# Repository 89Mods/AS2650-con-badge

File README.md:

## AS2650 Con Badge

Repo containing all the files for my latest con badge, using one of my GFMPW-0 ICs.

`HW` contains the KiCad project for the hardware.

`NB_Firmware` contains the management controller firmware.

`CPLD` contains the Quartus project for the CPLD on the board.

`Verilog` contains a complete Verilog model of the whole board, including the LED screen (requires gtkmm-4.0 to display).

`Software` is the actual meat of the project - all the code running on the badge.

`Bitmaps` contains all image assets to be placed into ROM.

Some misc stuff:

`ObjParser.java` converts .obj 3D model files to the format used by my rasterizer implementation.

`ROM_layout` visualizes the layout of the SPI flash accessible by the AS2650.

`ROMGlue` is a very long script that grabs all the different built binaries and asset files, and puts it also into a single ROM image, according to the documented layout.

`Avali.bin` is the 3D model data rendered by one of the demos.

There is also a (very ugly) Makefile to build parts of the project.

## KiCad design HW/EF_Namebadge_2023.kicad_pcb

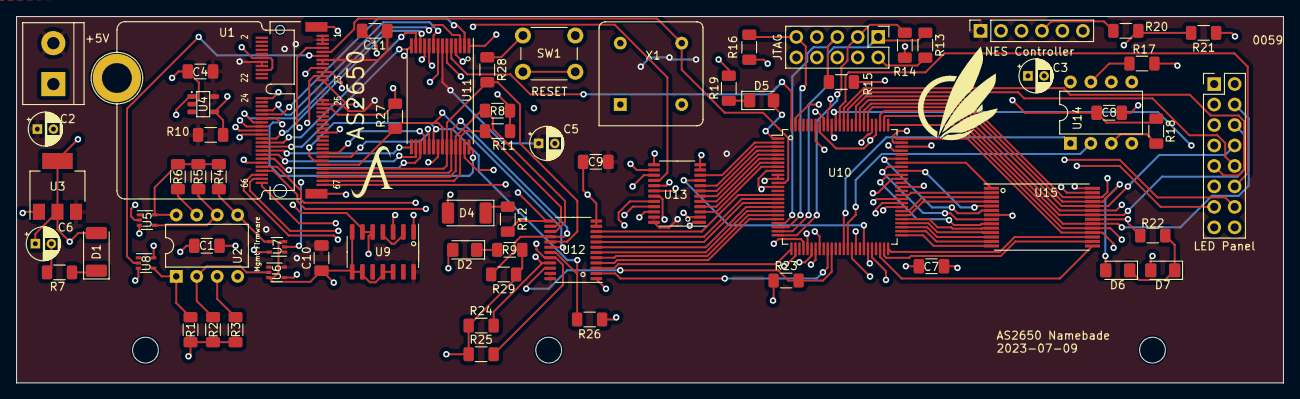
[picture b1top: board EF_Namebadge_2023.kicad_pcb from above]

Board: 4 copper layers, 157.2 x 45.5 mm, 71 parts (0 on the bottom side), 124 nets.

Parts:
C1, C4, C7, C8, C9, C10, C11: 0.1µF; C_1206_3216Metric_Pad1.33x1.80mm_HandSolder
C2, C5, C6: 1µF; CP_Radial_D4.0mm_P2.00mm
C3: 10µF; CP_Radial_D4.0mm_P2.00mm
D1, D4: LED; LED_2010_5025Metric_Pad1.52x2.65mm_HandSolder
D2, D5, D6, D7: LED; LED_1206_3216Metric_Pad1.42x1.75mm_HandSolder
H1: MICROMOD-Standoff; MicroMod-Standoff
H2, H3, H4: MountingHole; MountingHole_3.2mm_M3_ISO7380
J1: Screw_Terminal_01x02; TerminalBlock_bornier-2_P5.08mm
J2: JTAG; PinHeader_2x05_P2.54mm_Vertical
J3: LED Panel; PinHeader_2x08_P2.54mm_Vertical
J4: NES Controller; PinSocket_1x06_P2.54mm_Vertical
R1, R2, R4, R5: 100K; R_1206_3216Metric_Pad1.30x1.75mm_HandSolder
R3, R6, R7, R8, R9, R10, R11, R12, R13, R14, R15, R16, R17, R18, R23, R24, R25, R26, R27, R28, R29: 10K; R_1206_3216Metric_Pad1.30x1.75mm_HandSolder
R19, R20, R21, R22: 1K; R_1206_3216Metric_Pad1.30x1.75mm_HandSolder
SW1: SW_Push; SW_PUSH_6mm
U1: AS2650; M.2-CONNECTOR-E
U2, U14: W25Q32FVSS; DIP-8_W7.62mm
U3: AMS1117-3.3; SOT-223-3_TabPin2
U4: MCP1319MT-29LE-OT; PoR_5_SOT23
U5, U6, U7, U8: SN74LV1T34DCK; SOT-353_SC-70-5
U9: 74HC02; SOIC-14_3.9x8.7mm_P1.27mm
U10: EPM240T100; LQFP-100_14x14mm_P0.5mm
U11: AS7C256; TSOP-I-28_11.8x8mm_P0.55mm
U12, U13: SN74LVC8T245; TSSOP-24_4.4x7.8mm_P0.65mm
U15: 61LV256; TSOP-I-28_11.8x8mm_P0.55mm
X1: 25MHz; Oscillator_DIP-8

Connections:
+3V3: C1.1, C3.1, C6.1, C7.2, C8.2, D1.2 (A), J2.4, R1.2, R2.2, R3.2, R4.2, R5.2, R6.2, R14.2, R15.2, R16.2, R17.1, R18.2, R23.1, U2.8 (VCC), U3.2 (VO), U5.5 (VCC), U7.5 (VCC), U8.5 (VCC), U10.9 (VCCIO1), U10.13 (VCCINT), U10.31 (VCCIO1), U10.45 (VCCIO1), U10.59 (VCCIO2), U10.63 (VCCINT), U10.80 (VCCIO2), U10.94 (VCCIO2), U12.1 (Vcca), U13.1 (Vcca), U14.8 (VCC), U15.7 (Vdd), X1.8 (Vcc)
+5V: C2.1, C4.2, C5.1, C9.2, C10.2, C11.2, J1.2, J4.1, R10.2, U1.1 (vccd2), U1.3 (vddio), U1.5 (vdda), U1.13 (vdda2), U1.14 (vccd), U1.15 (vcdd), U1.16 (vddio), U1.33 (vdda1), U1.35 (vccd1), U3.3 (VI), U4.5 (VDD), U6.5 (VCC), U9.14 (VCC), U11.7 (Vcc), U12.23 (Vccb), U12.24 (Vccb), U13.23 (Vccb), U13.24 (Vccb)
A0: U1.62 (mprj_io[20]), U11.17 (A0)
A1: U1.60 (mprj_io[21]), U11.16 (A1)
A2: U1.58 (mprj_io[22]), U11.15 (A2)
A3: U1.56 (mprj_io[23]), U11.14 (A3)
A4: U1.54 (mprj_io[24]), U11.13 (A4)
A5: U1.52 (mprj_io[25]), U11.12 (A5)
A6: U1.50 (mprj_io[26]), U11.11 (A6)
A7: U1.48 (mprj_io[27]), U11.10 (A7)
A8: U1.46 (mprj_io[28]), U11.4 (A8)
A9: U1.44 (mprj_io[29]), U11.3 (A9)
A10: U1.42 (mprj_io[30]), U11.28 (A10)
A11: U1.40 (mprj_io[31]), U11.2 (A11)
A12: U1.38 (mprj_io[32]), U11.9 (A12), U13.16 (B6)
A12_3.3: U10.3 (IO1_3), U13.8 (A6)
A13: U10.100 (IO2_100), U11.5 (A13)
A14: U10.99 (IO2_99), U11.8 (A14)
BUS_DIR: U10.35 (IO1_35), U12.2 (DIR)
DB0: R24.2, U1.59 (mprj_io[5]_ser_rx), U11.18 (I/O0), U12.21 (B1)
DB0_3.3: U10.26 (IO1_26), U12.3 (A1)
DB1: R25.2, U1.61 (mprj_io[6]_ser_tx), U11.19 (I/O1), U12.20 (B2)
DB1_3.3: U10.21 (IO1_21), U12.4 (A2)
DB2: R26.2, U1.63 (mprj_io[7]), U11.20 (I/O2), U12.19 (B3)
DB2_3.3: U10.20 (IO1_20), U12.5 (A3)
DB3: R27.2, U1.65 (mprj_io[8]), U11.22 (I/O3), U12.18 (B4)
DB3_3.3: U10.19 (IO1_19), U12.6 (A4)
DB4: R28.2, U1.67 (mprj_io[9]), U11.23 (I/O4), U12.17 (B5)
DB4_3.3: U10.18 (IO1_18), U12.7 (A5)
DB5: R29.2, U1.69 (mprj_io[10]), U11.24 (I/O5), U12.16 (B6)
DB5_3.3: U10.17 (IO1_17), U12.8 (A6)
DB6: R8.2, U1.71 (mprj_io[11]), U11.25 (I/O6), U12.15 (B7)
DB6_3.3: U10.16 (IO1_16), U12.9 (A7)
DB7: R11.2, U1.73 (mprj_io[12]), U11.26 (I/O7), U12.14 (B8)
DB7_3.3: U10.15 (IO1_15), U12.10 (A8)
DISP_A: J3.10, U10.86 (IO2_86)
DISP_B: J3.9, U10.87 (IO2_87)
DISP_C: J3.12, U10.88 (IO2_88)
DISP_CLK: J3.14, U10.73 (IO2_73)
DISP_D: J3.11, U10.89 (IO2_89)
DISP_OE: J3.16, U10.74 (IO2_74)
DISP_STB: J3.13, U10.72 (IO2_72)
D/~C: U1.74 (mprj_io[14]), U13.21 (B1)
D/~C_3.3: U10.8 (IO1_8), U13.3 (A1)
FIRM_CS: R1.1, U2.1 (~CS), U8.4 (Y)
FIRM_SCK: R5.1, U2.6 (SCK), U5.4 (Y)
FIRM_SI: R4.1, U2.5 (SI(D0)), U7.4 (Y)
FIRM_SO: R2.1, U2.2 (SO(D1)), U6.2 (A)
Flag: D2.2 (A), U1.64 (mprj_io[19])
GND: C1.2, C2.2, C3.2, C4.1, C5.2, C6.2, C7.1, C8.1, C9.1, C10.1, C11.1, J1.1, J2.2, J2.10, J3.3, J3.7, J3.15, J4.5, J4.6, R7.2, R8.1, R9.2, R11.1, R12.2, R13.2, R19.2, R21.1, R22.2, R24.1, R25.1, R26.1, R27.1, R28.1, R29.1, SW1.1, U1.12 (GND), U1.18 (GND), U1.37 (GND), U1.A1 (GND), U1.A2 (GND), U2.4 (GND), U3.1 (GND), U4.2 (VSS), U5.3 (GND), U6.3 (GND), U7.3 (GND), U8.3 (GND), U9.7 (GND), U9.8, U9.9, U9.11, U9.12, U10.10 (GNDIO), U10.11 (GNDINT), U10.32 (GNDIO), U10.46 (GNDIO), U10.60 (GNDIO), U10.65 (GNDINT), U10.79 (GNDIO), U10.93 (GNDIO), U11.21 (GND), U12.11 (GND), U12.12 (GND), U12.13 (GND), U13.2 (DIR), U13.11 (GND), U13.12 (GND), U13.13 (GND), U13.22 (~OE), U14.4 (GND), U15.21 (GND), U15.27 (~CE), X1.4 (GND)
LVL_SHIFT_EN: R23.2, U10.36 (IO1_36), U12.22 (~OE)
M/~IO: U1.72 (mprj_io[15]), U13.20 (B2)
M/~IO_3.3: U10.7 (IO1_7), U13.4 (A2)
NES_CLK: J4.2, U10.29 (IO1_29)
NES_DATA: R20.1, R21.2, U10.33 (IO1_33)
NES_LATCH: J4.3, U10.30 (IO1_30)
unnamed: D1.1 (K), R7.1
unnamed: D2.1 (K), R9.1
unnamed: D4.1 (K), R12.1
unnamed: D5.2 (A), U10.1 (IO2_1)
unnamed: D5.1 (K), R19.1
unnamed: D6.1 (K), D7.1 (K), R22.1
unnamed: J2.1, R13.1, U10.24 (TCK)
unnamed: J2.3, R14.1, U10.25 (TDO)
unnamed: J2.5, R15.1, U10.22 (TMS)
unnamed: J2.9, R16.1, U10.23 (TDI)
unnamed: J4.4, R20.2
unnamed: U1.11 (Caravel_CSB), U8.2 (A)
unnamed: U1.17 (Caravel_D0), U7.2 (A)
unnamed: U1.19 (Caravel_D1), U6.4 (Y)
unnamed: U1.23 (Caravel_SCK), U5.2 (A)
unnamed: U1.7 (~RST), U9.1
unnamed: R6.1, U2.7 (~HOLD(D3))
unnamed: R3.1, U2.3 (~WP(D2))
unnamed: R10.1, SW1.2, U4.4 (~MR)
unnamed: U9.2, U9.4
unnamed: U10.2 (IO1_2), U13.10 (A8)
unnamed: R17.2, U14.7 (~HOLD(D3))
unnamed: R18.1, U14.3 (~WP(D2))
OPREQ: U1.68 (mprj_io[17]), U13.18 (B4)
OPREQ_3.3: U10.5 (IO1_5), U13.6 (A4)
POR: U4.1 (~RST), U9.5, U9.6, U13.15 (B7)
POR_3.3: U10.44 (IO1_44/DEV_CLRn), U13.9 (A7)
R/~W: U1.66 (mprj_io[18]), U13.17 (B5)
R/~W_3.3: U10.4 (IO1_4), U13.7 (A5)
SPI_SCK: U10.41 (IO1_41), U14.6 (SCK)
SPI_SI: U10.40 (IO1_40), U14.2 (SO(D1))
SPI_SO: U10.42 (IO1_42), U14.5 (SI(D0))
Sense: U1.75 (mprj_io[13]), U10.27 (IO1_27)
VRAM_AD0: U10.50 (IO1_50), U15.17 (A0)
VRAM_AD1: U10.49 (IO1_49), U15.16 (A1)
VRAM_AD2: U10.48 (IO1_48), U15.15 (A2)
VRAM_AD3: U10.51 (IO1_51), U15.14 (A3)
VRAM_AD4: U10.52 (IO2_52), U15.13 (A4)
VRAM_AD5: U10.53 (IO2_53), U15.12 (A5)
VRAM_AD6: U10.54 (IO2_54), U15.11 (A6)
VRAM_AD7: U10.55 (IO2_55), U15.10 (A7)
VRAM_AD8: U10.56 (IO2_56), U15.4 (A8)
VRAM_AD9: U10.57 (IO2_57), U15.3 (A9)
VRAM_AD10: U10.58 (IO2_58), U15.28 (A10)
VRAM_AD11: U10.61 (IO2_61), U15.2 (A11)
VRAM_AD12: U10.66 (IO2_66), U15.9 (A12)
VRAM_AD13: U10.67 (IO2_67), U15.5 (A13)
VRAM_AD14: U10.68 (IO2_68), U15.8 (A14)
VRAM_D0: J3.2, U10.75 (IO2_75), U15.18 (IO0)
VRAM_D1: J3.1, U10.76 (IO2_76), U15.19 (IO1)
VRAM_D2: J3.4, U10.77 (IO2_77), U15.20 (IO2)
VRAM_D3: J3.6, U10.78 (IO2_78), U15.22 (IO3)
VRAM_D4: J3.5, U10.81 (IO2_81), U15.23 (IO4)
VRAM_D5: J3.8, U10.82 (IO2_82), U15.24 (IO5)
VRAM_D6: D6.2 (A), U10.83 (IO2_83), U15.25 (IO6)
VRAM_D7: D7.2 (A), U10.84 (IO2_84), U15.26 (IO7)
WRP: U1.70 (mprj_io[16]), U13.19 (B3)
WRP_3.3: U10.6 (IO1_6), U13.5 (A3)
cpld_rst: U1.32 (mprj_io[35]), U13.14 (B8)
crvl_led: D4.2 (A), U1.49 (mprj_io[0])
gpio: U1.21 (gpio), U9.3
xclk: U1.9 (xclk), U10.12 (IO1_12/GCLK0), X1.5 (OUT)
~RAM_CE: U10.90 (IO2_90), U11.27 (~CE)
~RAM_OE: U10.91 (IO2_91), U11.1 (~OE)
~RAM_WE: U10.92 (IO2_92), U11.6 (~WE)
~SPI_CS: U10.39 (IO1_39), U14.1 (~CS)
~VRAM_OE: U10.69 (IO2_69), U15.1 (~OE)
~VRAM_WE: U10.70 (IO2_70), U15.6 (~WE)

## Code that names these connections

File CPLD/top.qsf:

# -------------------------------------------------------------------------- #
#
# Copyright (C) 2023  Intel Corporation. All rights reserved.
# Your use of Intel Corporation's design tools, logic functions 
# and other software and tools, and any partner logic 
# functions, and any output files from any of the foregoing 
# (including device programming or simulation files), and any 
# associated documentation or information are expressly subject 
# to the terms and conditions of the Intel Program License 
# Subscription Agreement, the Intel Quartus Prime License Agreement,
# the Intel FPGA IP License Agreement, or other applicable license
# agreement, including, without limitation, that your use is for
# the sole purpose of programming logic devices manufactured by
# Intel and sold by Intel or its authorized distributors.  Please
# refer to the applicable agreement for further details, at
# https://fpgasoftware.intel.com/eula.
#
# -------------------------------------------------------------------------- #
#
# Quartus Prime
# Version 22.1std.1 Build 917 02/14/2023 SC Lite Edition
# Date created = 17:04:29  June 30, 2023
#
# -------------------------------------------------------------------------- #
#
# Notes:
#
# 1) The default values for assignments are stored in the file:
#		top_assignment_defaults.qdf
#    If this file doesn't exist, see file:
#		assignment_defaults.qdf
#
# 2) Intel recommends that you do not modify this file. This
#    file is updated automatically by the Quartus Prime software
#    and any changes you make may be lost or overwritten.
#
# -------------------------------------------------------------------------- #


set_global_assignment -name FAMILY "MAX II"
set_global_assignment -name DEVICE EPM240T100C5
set_global_assignment -name TOP_LEVEL_ENTITY top
set_global_assignment -name ORIGINAL_QUARTUS_VERSION 22.1STD.1
set_global_assignment -name PROJECT_CREATION_TIME_DATE "17:04:29  JUNE 30, 2023"
set_global_assignment -name LAST_QUARTUS_VERSION "22.1std.2 Lite Edition"
set_global_assignment -name PROJECT_OUTPUT_DIRECTORY output_files
set_global_assignment -name MIN_CORE_JUNCTION_TEMP 0
set_global_assignment -name MAX_CORE_JUNCTION_TEMP 85
set_global_assignment -name DEVICE_FILTER_PACKAGE TQFP
set_global_assignment -name DEVICE_FILTER_PIN_COUNT 100
set_global_assignment -name ERROR_CHECK_FREQUENCY_DIVISOR "-1"
set_global_assignment -name POWER_EXT_SUPPLY_VOLTAGE_TO_REGULATOR 3.3V
set_location_assignment PIN_5 -to opreq
set_location_assignment PIN_4 -to rw
set_location_assignment PIN_6 -to wrp
set_location_assignment PIN_12 -to clk
set_location_assignment PIN_15 -to dbus[7]
set_location_assignment PIN_16 -to dbus[6]
set_location_assignment PIN_17 -to dbus[5]
set_location_assignment PIN_18 -to dbus[4]
set_location_assignment PIN_19 -to dbus[3]
set_location_assignment PIN_20 -to dbus[2]
set_location_assignment PIN_21 -to dbus[1]
set_location_assignment PIN_26 -to dbus[0]
set_instance_assignment -name IO_STANDARD "3.3-V LVTTL" -to A12
set_instance_assignment -name IO_STANDARD "3.3-V LVTTL" -to DISP_addr[1]
set_location_assignment PIN_3 -to A12
set_location_assignment PIN_100 -to A13
set_location_assignment PIN_99 -to A14
set_location_assignment PIN_86 -to DISP_addr[0]
set_location_assignment PIN_87 -to DISP_addr[1]
set_location_assignment PIN_88 -to DISP_addr[2]
set_location_assignment PIN_89 -to DISP_addr[3]
set_location_assignment PIN_73 -to DISP_clk
set_location_assignment PIN_74 -to DISP_oeb
set_location_assignment PIN_72 -to DISP_stb
set_location_assignment PIN_29 -to NES_clk
set_location_assignment PIN_33 -to NES_data
set_location_assignment PIN_91 -to RAM_oeb
set_location_assignment PIN_90 -to RAM_ceb
set_location_assignment PIN_92 -to RAM_web
set_location_assignment PIN_27 -to sense
set_location_assignment PIN_7 -to m_io
set_location_assignment PIN_36 -to lvl_shift_enb
set_location_assignment PIN_2 -to cpld_rst
set_location_assignment PIN_8 -to d_c
set_location_assignment PIN_35 -to bus_dir
set_location_assignment PIN_70 -to VRAM_web
set_location_assignment PIN_69 -to VRAM_oeb
set_location_assignment PIN_84 -to VRAM_data[7]
set_location_assignment PIN_83 -to VRAM_data[6]
set_location_assignment PIN_82 -to VRAM_data[5]
set_location_assignment PIN_81 -to VRAM_data[4]
set_location_assignment PIN_78 -to VRAM_data[3]
set_location_assignment PIN_77 -to VRAM_data[2]
set_location_assignment PIN_76 -to VRAM_data[1]
set_location_assignment PIN_75 -to VRAM_data[0]
set_location_assignment PIN_68 -to VRAM_addr[14]
set_location_assignment PIN_67 -to VRAM_addr[13]
set_location_assignment PIN_66 -to VRAM_addr[12]
set_location_assignment PIN_44 -to POR
set_location_assignment PIN_30 -to NES_latch
set_location_assignment PIN_39 -to SPI_csb
set_location_assignment PIN_41 -to SPI_sck
set_location_assignment PIN_40 -to SPI_si
set_location_assignment PIN_42 -to SPI_so
set_location_assignment PIN_61 -to VRAM_addr[11]
set_location_assignment PIN_58 -to VRAM_addr[10]
set_location_assignment PIN_57 -to VRAM_addr[9]
set_location_assignment PIN_56 -to VRAM_addr[8]
set_location_assignment PIN_55 -to VRAM_addr[7]
set_location_assignment PIN_54 -to VRAM_addr[6]
set_location_assignment PIN_53 -to VRAM_addr[5]
set_location_assignment PIN_52 -to VRAM_addr[4]
set_location_assignment PIN_51 -to VRAM_addr[3]
set_location_assignment PIN_48 -to VRAM_addr[2]
set_location_assignment PIN_49 -to VRAM_addr[1]
set_location_assignment PIN_50 -to VRAM_addr[0]
set_location_assignment PIN_1 -to LED
set_instance_assignment -name IO_STANDARD "3.3-V LVTTL" -to RAM_ceb
set_instance_assignment -name IO_STANDARD "3.3-V LVTTL" -to RAM_oeb
set_instance_assignment -name IO_STANDARD "3.3-V LVCMOS" -to RAM_web
set_instance_assignment -name IO_STANDARD "3.3-V LVCMOS" -to A13
set_instance_assignment -name IO_STANDARD "3.3-V LVCMOS" -to A14
set_instance_assignment -name IO_STANDARD "3.3-V LVTTL" -to dbus[7]
set_instance_assignment -name IO_STANDARD "3.3-V LVTTL" -to dbus[6]
set_instance_assignment -name IO_STANDARD "3.3-V LVTTL" -to dbus[5]
set_instance_assignment -name IO_STANDARD "3.3-V LVTTL" -to dbus[4]
set_instance_assignment -name IO_STANDARD "3.3-V LVTTL" -to dbus[3]
set_instance_assignment -name IO_STANDARD "3.3-V LVTTL" -to dbus[2]
set_instance_assignment -name IO_STANDARD "3.3-V LVTTL" -to dbus[1]
set_instance_assignment -name IO_STANDARD "3.3-V LVTTL" -to dbus
set_global_assignment -name SDC_FILE top.out.sdc
set_global_assignment -name VERILOG_FILE top.v
set_global_assignment -name POWER_PRESET_COOLING_SOLUTION "NO HEAT SINK WITH STILL AIR"

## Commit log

2023-09-26 Initial commit.
2023-09-26 gitignore update
